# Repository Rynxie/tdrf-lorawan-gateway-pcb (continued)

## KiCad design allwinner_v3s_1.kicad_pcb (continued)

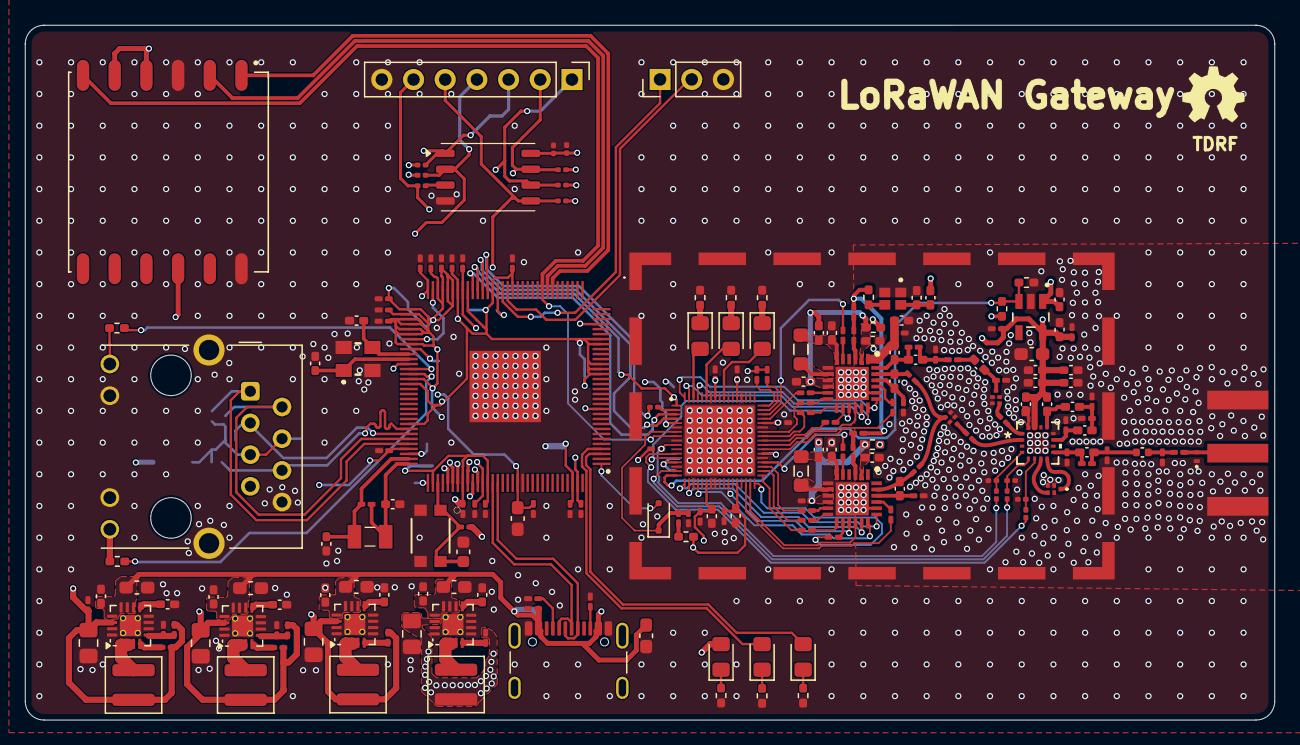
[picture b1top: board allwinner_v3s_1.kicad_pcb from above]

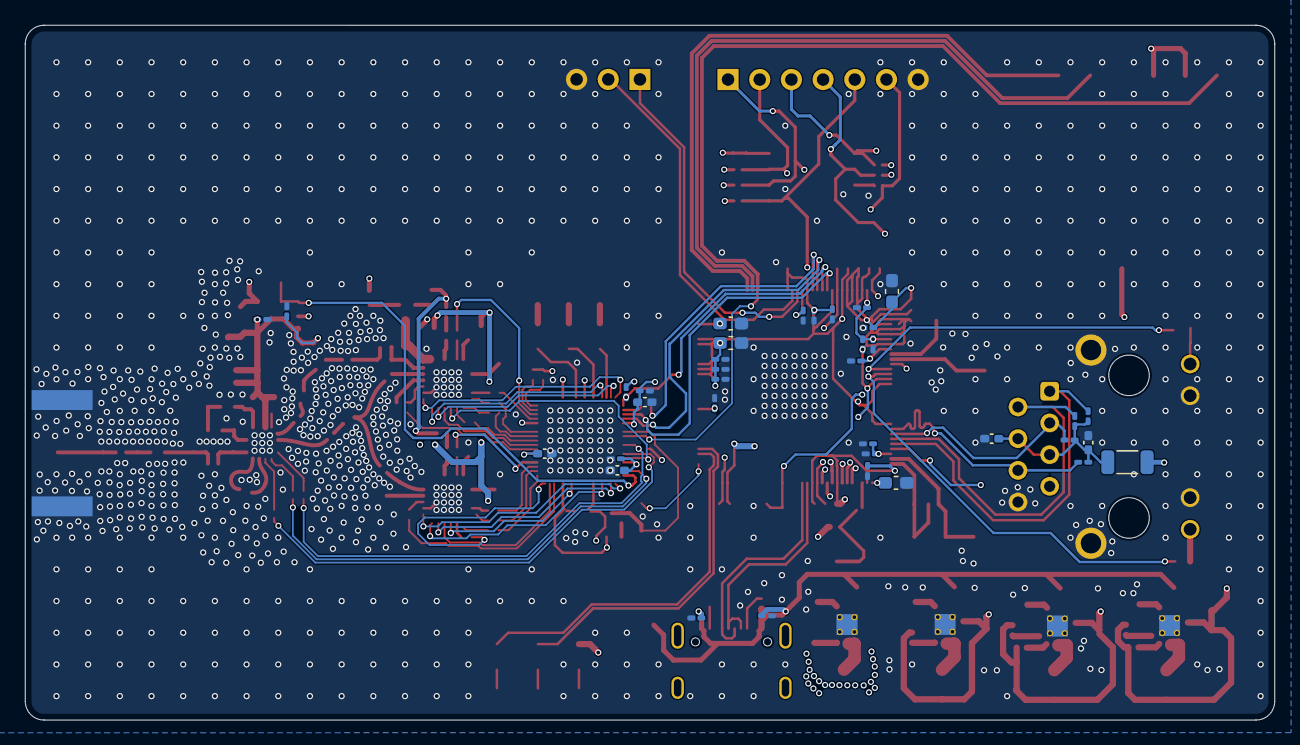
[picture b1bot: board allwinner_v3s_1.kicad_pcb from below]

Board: 4 copper layers, 100.2 x 55.7 mm, 235 parts (36 on the bottom side), 154 nets.

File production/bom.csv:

Designator,Footprint,Quantity,Value,LCSC Part #
"C1, C10, C104, C105, C107, C109, C110, C112, C113, C114, C14, C15, C16, C17, C2, C21, C22, C23, C24, C25, C26, C27, C28, C29, C3, C30, C32, C34, C35, C37, C4, C40, C41, C42, C44, C45, C46, C5, C6, C7, C8, C9",0201,42,100nF,
"C100, C38, C39",0201,3,10pF,
C101,0201,1,1.3pF,
"C102, C98",0402,2,27,
"C103, C106, C108, C111, C18, C19, C75, C82",0402,8,1uF,
"C11, C12",0402,2,470nF,
"C115, C31, C33, C61, C62, C71, C72",0402,7,100nF,
"C116, C117, C88",0201,3,100n,
"C13, C20, C36, C43, C47, C59, C60, C69, C70",0603,9,10uF,
C48,0402,1,47nF,
C49,0201,1,47pF,
C50,0603,1,2.2u,
"C51, C78, C80",0201,3,3.3pF,
C52,0201,1,5.6pF,
"C53, C54, C56, C57",0201,4,3.6pF,
C55,0201,1,39pF,
C58,0201,1,2.2pF,
"C63, C64, C73, C74",0402,4,3.3nF,
"C65, C66, C76, C85, C86, C87",0201,6,56pF,
"C67, C68, C81, C83",0805,4,22uF,
C77,0201,1,2.7pF,
C79,0201,1,1.5pF,
C84,0603,1,1u,
C89,0603,1,4.7uF,
C90,0402,1,10nF,
"C91, C95",0402,2,18,
C92,0402,1,1nF,
"C93, C96",0402,2,100n,
"C94, C97",0402,2,100pF,
C99,0201,1,DNP,
"D1, D2, D3, D4, D5, D6",0805,6,LED,
D7,D_SOD-323F,1,BAT54J,
FB1,0402,1,BLM15PG100SN1D,
"FL1, FL2, FL3",B39871B4377P810,3,B39871B4377P810,
"IC1, IC2",QFN50P400X400X100-25N-D,2,SX1250IMLTRT,
IC4,QFN35P700X700X80-69N-D,1,SX1302IMLTRT,
J1,TE_CONSMA020.062-G,1,Conn_Coaxial,
J2,PinHeader_1x03_P2.54mm_Vertical,1,Conn_01x03_Pin,
J3,RJ45_Hanrun_HR911105A_Horizontal,1,RJ45_Hanrun_HR911105A_Horizontal,
J5,USB_C_Receptacle_GCT_USB4105-xx-A_16P_TopMnt_Horizontal,1,USB_C_Receptacle_USB2.0_16P,
J6,PinHeader_1x07_P2.54mm_Vertical,1,Conn_01x07_Pin,
"L1, L2, R13",0402,3,NC,
"L10, L11, L13, L14",L_Coilcraft_XAL4020-XXX,4,2.2uH,
"L12, L15",0402,2,5.6nH,
L16,0402,1,1.2nH,
L17,1206,1,600Z,
L18,0402,1,6.8nH,
L19,0402,1,3nH,
L20,0402,1,7.5nH,
"L3, L4",0805,2,15uH,
L5,0402,1,47nH,
"L6, L9",0402,2,4.7nH,
"L7, L8",0402,2,12nH,
"R1, R2, R3",0402,3,0R,
"R10, R16, R9",0201,3,100kR,
R11,0201,1,75kR,
R12,0201,1,150kR,
R14,0402,1,100kR,
R15,0201,1,100k,
R17,0201,1,80.6kR,
R18,0201,1,220kR,
"R19, R20, R21",0201,3,1kR,
R22,0201,1,47k,
"R23, R24",0201,2,2k,
"R25, R26, R27, R28, R32, R35, R36, R38",0402,8,1k,
R29,0201,1,10M,
"R30, R31, R33, R34",0201,4,50,
"R37, R39, R62, R63, R64",0201,5,10K,
"R4, R5",0201,2,220R,
R40,0402,1,10R,
"R41, R42, R44",0201,3,47kR,
R43,0201,1,100R,
"R45, R46",0201,2,5.1kR,
"R47, R48, R49, R50, R51, R52, R53, R54, R55, R56, R57, R58",0201,12,0R,
"R59, R60",0201,2,4.7kR,
R6,0201,1,240,
R61,0201,1,22R,
"R7, R8",0201,2,12k,
SW1,KMR7_CNK,1,KMR731NG LFS,
U1,QFP40P1600X1600X160-129N,1,AllwinnerV3S,
U10,shield,1,BMI-S-205-C,
U11,SDTRUVAL_SDG02GWSIGA-CSNP2,1,SDG02GWSIGA-CSNP2,
U2,XCVR_L86M33,1,L86M33,
U3,VQFN-16-1EP_3x3mm_P0.5mm_EP1.68x1.68mm_ThermalVias,1,TPS62132,
"U4, U7",VQFN-16-1EP_3x3mm_P0.5mm_EP1.68x1.68mm_ThermalVias,2,TPS62130,
U5,Texas_DPY0002A_0.6x1mm_P0.65mm,1,ESD701DPYR,
U6,VQFN-16-1EP_3x3mm_P0.5mm_EP1.68x1.68mm_ThermalVias,1,TPS62131,
U8,SOT95P280X145-5N,1,TPS7A2033PDBVR,
U9,MCM16_3X3X0P75_SKY,1,SKY66420-11,
Y1,OSC_TX21-M010S-32.000-X-R,1,TX21-M010S-32.000-X-R,
Y2,ABS07,1,ABS07-32.768KHZ-7-T,
Y3,ABM810000MHZ12D2W,1,ABM8-24.000MHZ-B2-T,

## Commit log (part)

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2026-02-18 The ___ invisible ghost gerber curve trace deleted :)
2026-02-18 Gerbers generated
